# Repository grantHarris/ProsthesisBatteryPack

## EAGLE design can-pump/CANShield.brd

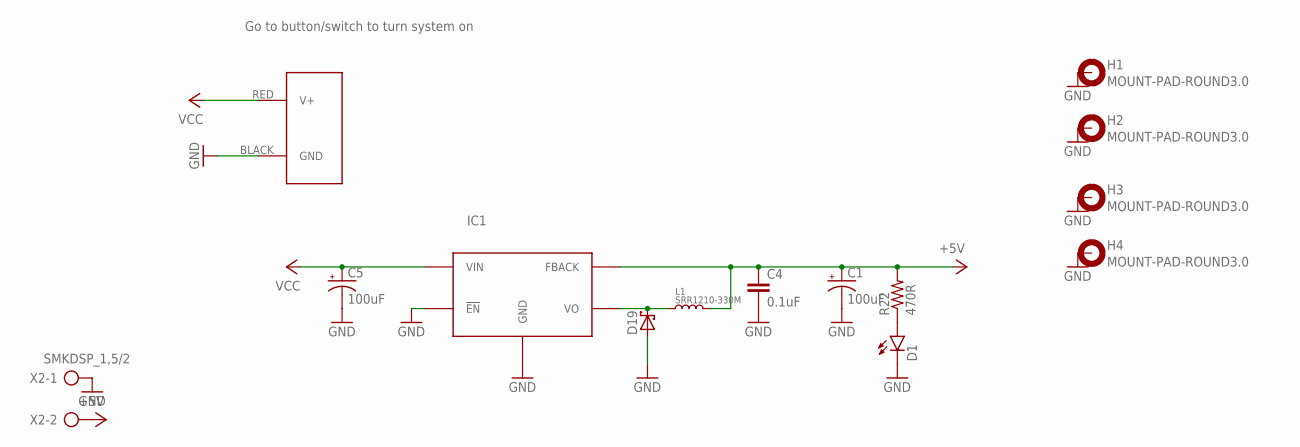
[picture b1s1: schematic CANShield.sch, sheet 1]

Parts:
C1, C5: 100uF; NIC_10X10.5_CAP
C4: 0.1uF; 0603-CAP
D1: LED1206; LED-1206
D19: SCHOTTKY-DIODESMC; SMC
H1, H2, H3, H4: MOUNT-PAD-ROUND3.0; 3,0-PAD
IC1: LM2576S; TO263-5
J1: POWERPOLE_POWER25A_HORIZONTAL_G2; POWERPOLE_PAIR_25A_HORIZ_G2
L1: SRR1210-330M; SRR1210
R22: 470R; 0603-RES
X2: SMKDSP_1,5/2

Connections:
+5V: C1.+, C4.1, IC1.4 (FBACK), L1.2, R22.2, X2.2; also elsewhere on the board
GND: C1.-, C4.2, C5.-, D1.C, D19.A, H1.B3,0, H2.B3,0, H3.B3,0, H4.B3,0, IC1.3 (GND), IC1.5 (!EN), IC1.TAB (GND), J1.BLACK (GND), X2.1; also elsewhere on the board
unnamed: D1.A, R22.1
unnamed: D19.C, IC1.2 (VO), L1.1
VCC: C5.+, IC1.1 (VIN), J1.RED (V+); also elsewhere on the board

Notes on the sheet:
Go to button/switch to turn system on

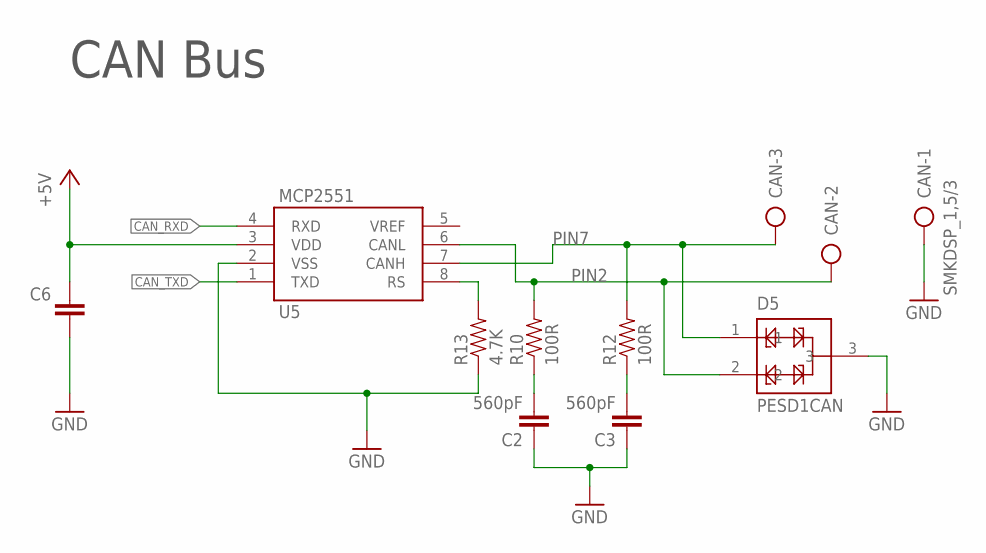
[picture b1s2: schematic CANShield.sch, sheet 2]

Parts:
C2, C3: 560pF; 0603-CAP
C6: 0.1uF; 0603-CAP
CAN: SMKDSP_1,5/3
D5: PESD1CAN; SOT23-3@1
R10, R12: 100R; 0603-RES@1
R13: 4.7K; 0603-RES@1
U5: MCP2551; SO08

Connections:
+5V: C6.2, U5.3 (VDD); also elsewhere on the board
CAN_RXD: U5.4 (RXD); also elsewhere on the board
CAN_TXD: U5.1 (TXD); also elsewhere on the board
GND: C2.1, C3.1, C6.1, CAN.1, D5.3, R13.1, U5.2 (VSS); also elsewhere on the board
unnamed: C2.2, R10.1
unnamed: C3.2, R12.1
unnamed: R13.2, U5.8 (RS)
PIN2: CAN.2, D5.2, R10.2, U5.6 (CANL)
PIN7: CAN.3, D5.1, R12.2, U5.7 (CANH)

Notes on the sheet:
CAN Bus

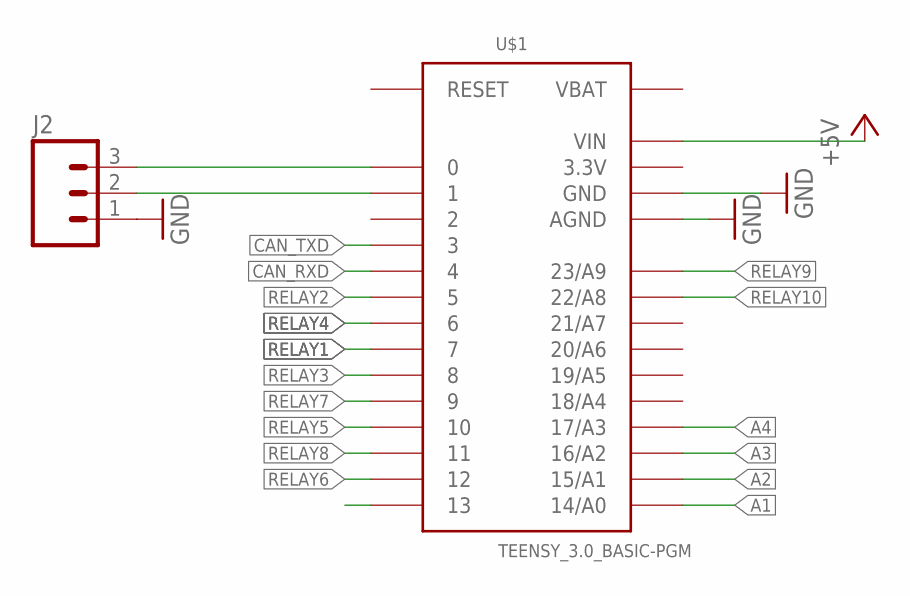
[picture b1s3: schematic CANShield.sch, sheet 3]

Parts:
J2: M03POLAR; MOLEX-1X3
U$1: TEENSY_3.0_BASIC-PGM

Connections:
3.3V: U$1.3.3V, U$1.3.3V1 (3.3V)
+5V: U$1.VIN; also elsewhere on the board
A1: U$1.14/A0; also elsewhere on the board
A2: U$1.15/A1; also elsewhere on the board
A3: U$1.16/A2; also elsewhere on the board
A4: U$1.17/A3; also elsewhere on the board
CAN_RXD: U$1.4; also elsewhere on the board
CAN_TXD: U$1.3; also elsewhere on the board
GND: J2.1, U$1.AGND, U$1.GND, U$1.GND1 (GND); also elsewhere on the board
unnamed: J2.3, U$1.0
unnamed: J2.2, U$1.1
RELAY1: U$1.7; also elsewhere on the board
RELAY2: U$1.5; also elsewhere on the board
RELAY3: U$1.8; also elsewhere on the board
RELAY4: U$1.6; also elsewhere on the board
RELAY5: U$1.10; also elsewhere on the board
RELAY6: U$1.12; also elsewhere on the board
RELAY7: U$1.9; also elsewhere on the board
RELAY8: U$1.11; also elsewhere on the board
RELAY9: U$1.23/A9; also elsewhere on the board
RELAY10: U$1.22/A8; also elsewhere on the board
VBAT: U$1.VBAT

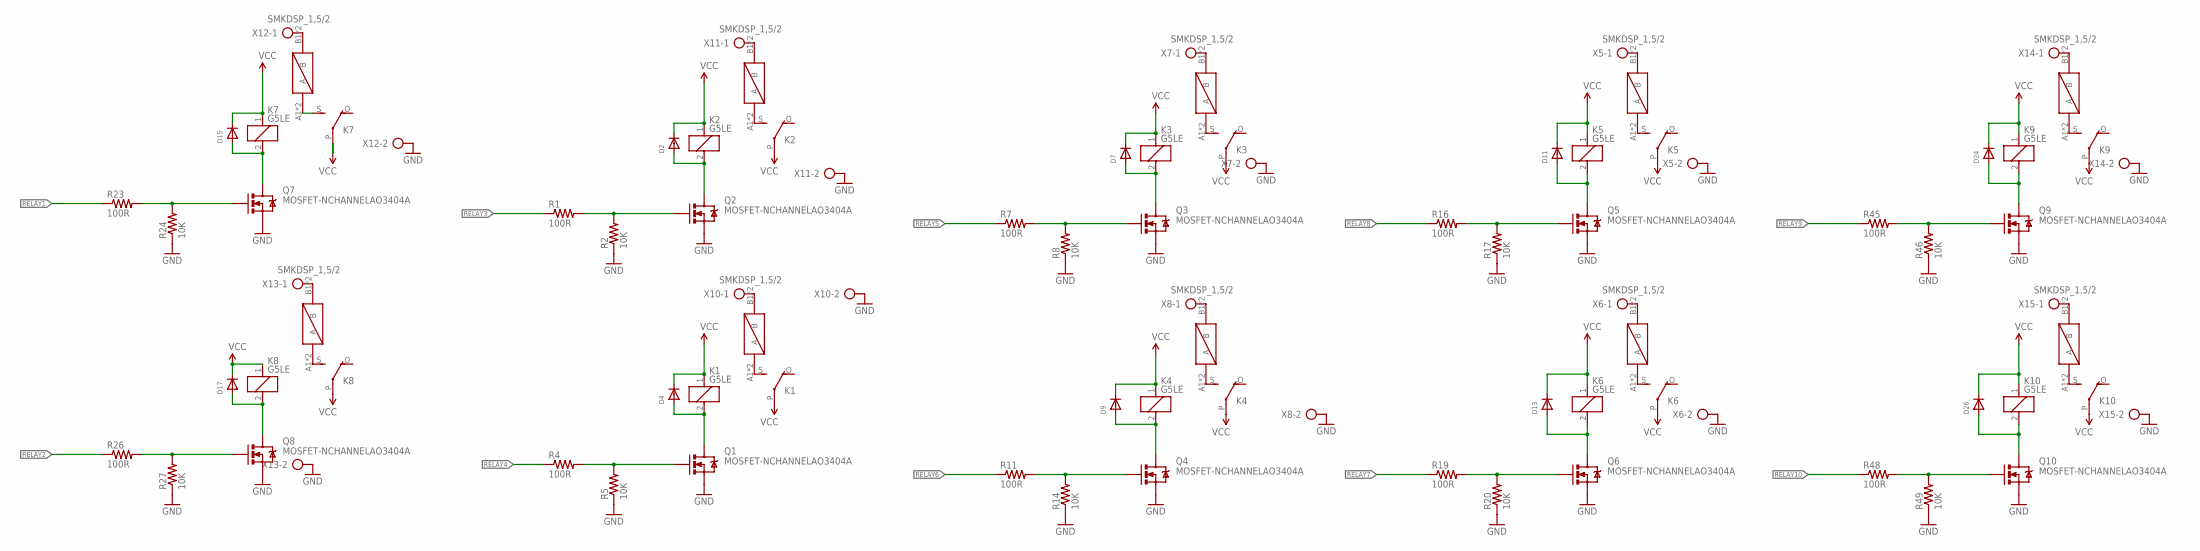
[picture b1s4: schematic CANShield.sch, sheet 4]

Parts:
D2, D4, D7, D9, D11, D13, D15, D17, D24, D26: DIODESOD-123; SOD-123
K1, K2, K3, K4, K5, K6, K7, K8, K9, K10: G5LE
Q1, Q2, Q3, Q4, Q5, Q6, Q7, Q8, Q9, Q10: MOSFET-NCHANNELAO3404A; SOT23-3
R1, R4, R7, R11, R16, R19, R23, R26, R45, R48: 100R; 0603-RES
R2, R5, R8, R14, R17, R20, R24, R27, R46, R49: 10K; 0603-RES
U$2, U$4, U$5, U$6, U$7, U$8, U$9, U$10, U$11, U$12: FUSE; MINIFUSE
X5, X6, X7, X8, X10, X11, X12, X13, X14, X15: SMKDSP_1,5/2

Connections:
GND: Q1.2 (S), Q2.2 (S), Q3.2 (S), Q4.2 (S), Q5.2 (S), Q6.2 (S), Q7.2 (S), Q8.2 (S), Q9.2 (S), Q10.2 (S), R2.1, R5.1, R8.1, R14.1, R17.1, R20.1, R24.1, R27.1, R46.1, R49.1, X5.2, X6.2, X7.2, X8.2, X10.2, X11.2, X12.2, X13.2, X14.2, X15.2; also elsewhere on the board
unnamed: Q2.1 (G), R1.2, R2.2
unnamed: D2.A, K2.2, Q2.3 (D)
unnamed: K3.S, U$7.A1 (A), U$7.A2 (A)
unnamed: K4.S, U$8.A1 (A), U$8.A2 (A)
unnamed: D4.A, K1.2, Q1.3 (D)
unnamed: Q1.1 (G), R4.2, R5.2
unnamed: U$8.B1 (B), U$8.B2 (B), X8.1
unnamed: D7.A, K3.2, Q3.3 (D)
unnamed: Q3.1 (G), R7.2, R8.2
unnamed: K6.S, U$9.A1 (A), U$9.A2 (A)
unnamed: D9.A, K4.2, Q4.3 (D)
unnamed: Q4.1 (G), R11.2, R14.2
unnamed: D11.A, K5.2, Q5.3 (D)
unnamed: Q5.1 (G), R16.2, R17.2
unnamed: D13.A, K6.2, Q6.3 (D)
unnamed: Q6.1 (G), R19.2, R20.2
unnamed: D15.A, K7.2, Q7.3 (D)
unnamed: Q7.1 (G), R23.2, R24.2
unnamed: D17.A, K8.2, Q8.3 (D)
unnamed: Q8.1 (G), R26.2, R27.2
unnamed: K2.S, U$4.A1 (A), U$4.A2 (A)
unnamed: K8.S, U$5.A1 (A), U$5.A2 (A)
unnamed: K7.S, U$2.A1 (A), U$2.A2 (A)
unnamed: K1.S, U$6.A1 (A), U$6.A2 (A)
unnamed: D24.A, K9.2, Q9.3 (D)
unnamed: Q9.1 (G), R45.2, R46.2
unnamed: D26.A, K10.2, Q10.3 (D)
unnamed: Q10.1 (G), R48.2, R49.2
unnamed: K9.S, U$11.A1 (A), U$11.A2 (A)
unnamed: K10.S, U$12.A1 (A), U$12.A2 (A)
unnamed: U$2.B1 (B), U$2.B2 (B), X12.1
unnamed: U$5.B1 (B), U$5.B2 (B), X13.1
unnamed: U$4.B1 (B), U$4.B2 (B), X11.1
unnamed: U$6.B1 (B), U$6.B2 (B), X10.1
unnamed: U$9.B1 (B), U$9.B2 (B), X6.1
unnamed: K5.S, U$10.A1 (A), U$10.A2 (A)
unnamed: U$7.B1 (B), U$7.B2 (B), X7.1
unnamed: U$10.B1 (B), U$10.B2 (B), X5.1
unnamed: U$12.B1 (B), U$12.B2 (B), X15.1
unnamed: U$11.B1 (B), U$11.B2 (B), X14.1
RELAY1: R23.1; also elsewhere on the board
RELAY2: R26.1; also elsewhere on the board
RELAY3: R1.1; also elsewhere on the board
RELAY4: R4.1; also elsewhere on the board
RELAY5: R7.1; also elsewhere on the board
RELAY6: R11.1; also elsewhere on the board
RELAY7: R19.1; also elsewhere on the board
RELAY8: R16.1; also elsewhere on the board
RELAY9: R45.1; also elsewhere on the board
RELAY10: R48.1; also elsewhere on the board
VCC: D2.C, D4.C, D7.C, D9.C, D11.C, D13.C, D15.C, D17.C, D24.C, D26.C, K1.1, K1.P, K2.1, K2.P, K3.1, K3.P, K4.1, K4.P, K5.1, K5.P, K6.1, K6.P, K7.1, K7.P, K8.1, K8.P, K9.1, K9.P, K10.1, K10.P; also elsewhere on the board

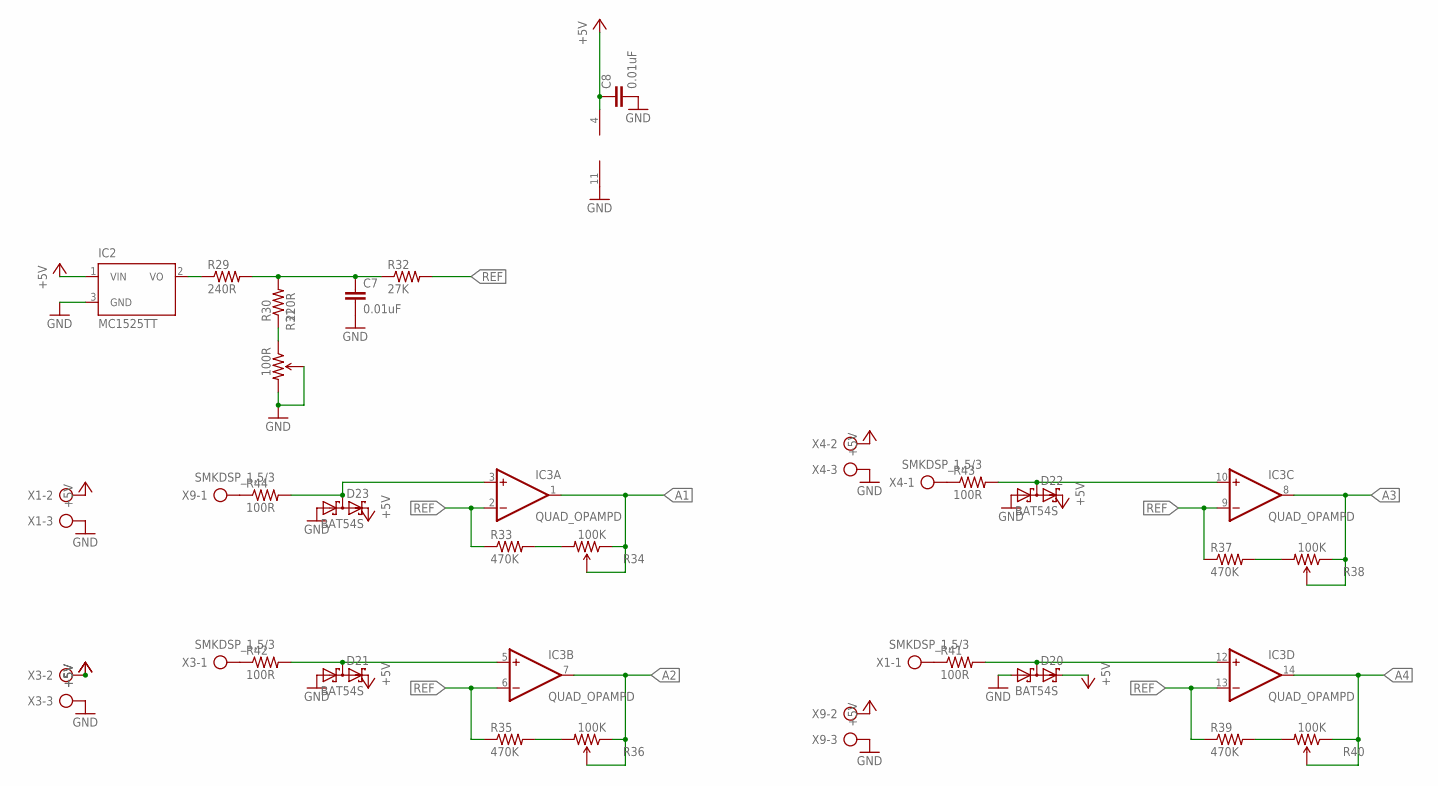
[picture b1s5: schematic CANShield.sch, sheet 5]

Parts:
C7, C8: 0.01uF; 0603-CAP
D20, D21, D22, D23: BAT54S; SOT23
IC2: MC1525TT; SOT23
IC3: QUAD_OPAMPD; SO14
R29: 240R; 0603-RES
R30: 220R; 0603-RES
R31: 100R; TRIMPOT-3MM
R32: 27K; 0603-RES
R33, R35, R37, R39: 470K; 0603-RES
R34, R36, R38, R40: 100K; TRIMPOT-3MM
R41, R42, R43, R44: 100R; 0603-RES
X1, X3, X4, X9: SMKDSP_1,5/3

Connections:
+5V: C8.1, D20.2 (C2), D21.2 (C2), D22.2 (C2), D23.2 (C2), IC2.1 (VIN), IC3.4 (V+), X1.2, X3.2, X4.2, X9.2; also elsewhere on the board
A1: IC3.1 (OUT), R34.1 (CCW), R34.2 (WIPER); also elsewhere on the board
A2: IC3.7 (OUT), R36.1 (CCW), R36.2 (WIPER); also elsewhere on the board
A3: IC3.8 (OUT), R38.1 (CCW), R38.2 (WIPER); also elsewhere on the board
A4: IC3.14 (OUT), R40.1 (CCW), R40.2 (WIPER); also elsewhere on the board
GND: C7.2, C8.2, D20.1 (A1), D21.1 (A1), D22.1 (A1), D23.1 (A1), IC2.3 (GND), IC3.11 (V-), R31.2 (WIPER), R31.3 (CW), X1.3, X3.3, X4.3, X9.3; also elsewhere on the board
unnamed: R44.1, X9.1
unnamed: R42.1, X3.1
unnamed: R43.1, X4.1
unnamed: R41.1, X1.1
unnamed: IC2.2 (VO), R29.1
unnamed: C7.1, R29.2, R30.2, R32.1
unnamed: R30.1, R31.1 (CCW)
unnamed: R33.2, R34.3 (CW)
unnamed: D21.3 (C1A2), IC3.5 (+IN), R42.2
unnamed: D20.3 (C1A2), IC3.12 (+IN), R41.2
unnamed: R35.2, R36.3 (CW)
unnamed: D23.3 (C1A2), IC3.3 (+IN), R44.2
unnamed: R39.2, R40.3 (CW)
unnamed: R37.2, R38.3 (CW)
unnamed: D22.3 (C1A2), IC3.10 (+IN), R43.2
REF: IC3.2 (-IN), IC3.6 (-IN), IC3.9 (-IN), IC3.13 (-IN), R32.2, R33.1, R35.1, R37.1, R39.1

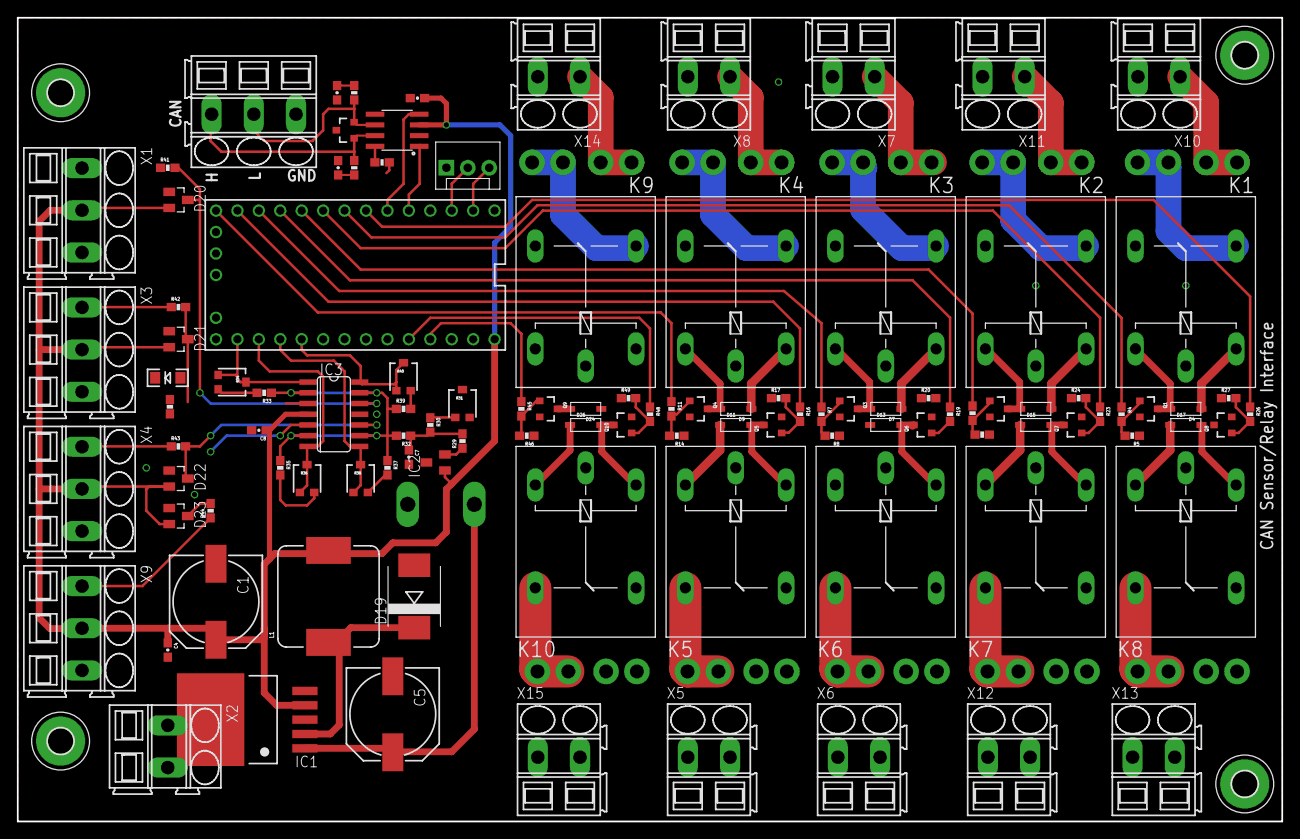
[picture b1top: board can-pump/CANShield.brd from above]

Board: 2 copper layers, 149.9 x 95.2 mm, 124 parts (1 on the bottom side), 85 nets.

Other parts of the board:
U$3: PROS_LOGO

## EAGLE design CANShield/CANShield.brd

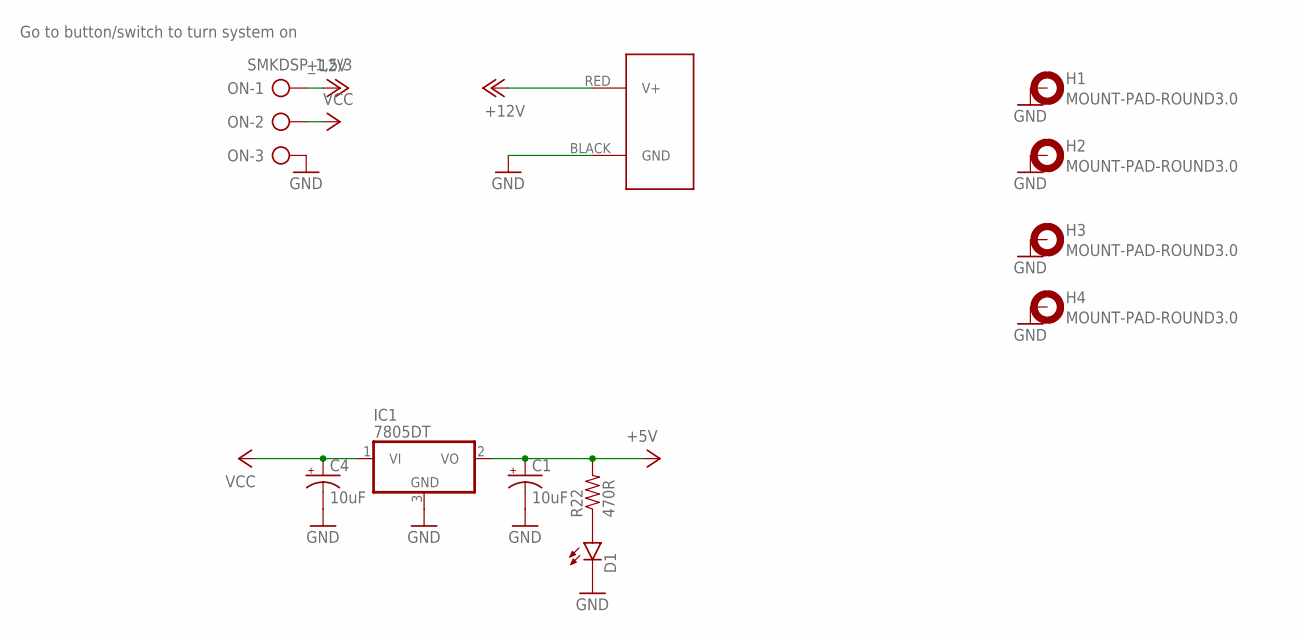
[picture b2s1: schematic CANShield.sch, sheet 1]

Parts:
C1, C4: 10uF; PANASONIC_C
D1: LED1206; LED-1206
H1, H2, H3, H4: MOUNT-PAD-ROUND3.0; 3,0-PAD
IC1: 7805DT; TO252
J2: POWERPOLE_POWER25A_HORIZONTAL_G2; POWERPOLE_PAIR_25A_HORIZ_G2
ON: SMKDSP_1,5/3
R22: 470R; 0603-RES

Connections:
+5V: C1.+, IC1.2 (VO), R22.2; also elsewhere on the board
+12V: J2.RED (V+), ON.1; also elsewhere on the board
GND: C1.-, C4.-, D1.C, H1.B3,0, H2.B3,0, H3.B3,0, H4.B3,0, IC1.3 (GND), J2.BLACK (GND), ON.3; also elsewhere on the board
unnamed: D1.A, R22.1
VCC: C4.+, IC1.1 (VI), ON.2

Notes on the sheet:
Go to button/switch to turn system on

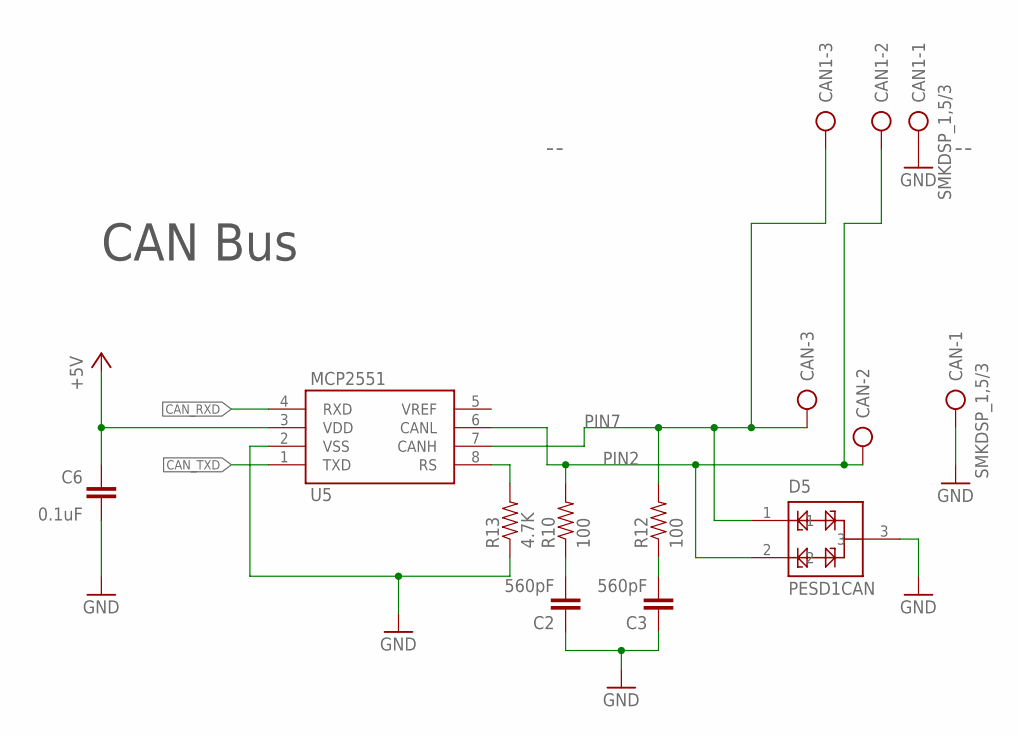
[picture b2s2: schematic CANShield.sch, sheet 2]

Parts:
C2, C3: 560pF; 0603-CAP
C6: 0.1uF; 0603-CAP
CAN, CAN1: SMKDSP_1,5/3
D5: PESD1CAN; SOT23-3@1
R10, R12: 100; 0603-RES@1
R13: 4.7K; 0603-RES@1
U5: MCP2551; SO08

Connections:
+5V: C6.2, U5.3 (VDD); also elsewhere on the board
CAN_RXD: U5.4 (RXD); also elsewhere on the board
CAN_TXD: U5.1 (TXD); also elsewhere on the board
GND: C2.1, C3.1, C6.1, CAN.1, CAN1.1, D5.3, R13.1, U5.2 (VSS); also elsewhere on the board
unnamed: C2.2, R10.1
unnamed: C3.2, R12.1
unnamed: R13.2, U5.8 (RS)
PIN2: CAN.2, CAN1.2, D5.2, R10.2, U5.6 (CANL)
PIN7: CAN.3, CAN1.3, D5.1, R12.2, U5.7 (CANH)

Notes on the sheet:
CAN Bus

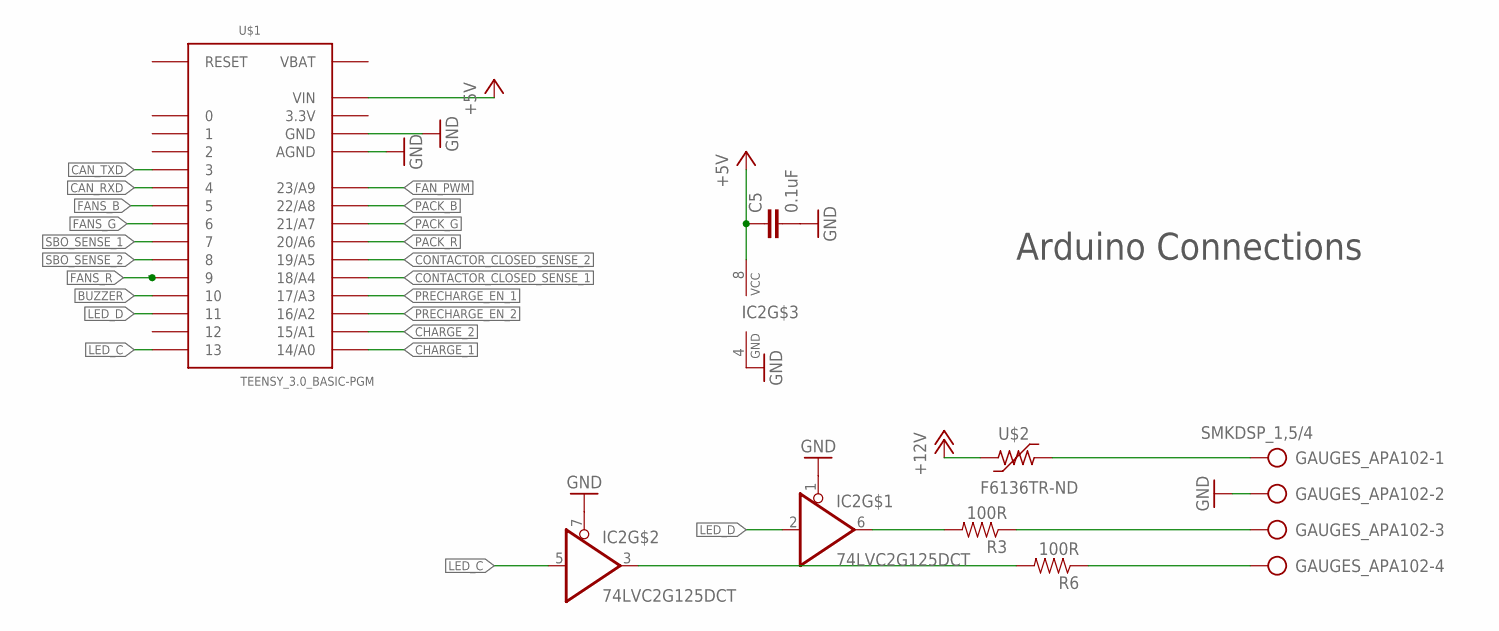
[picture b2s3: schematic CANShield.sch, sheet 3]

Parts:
C5: 0.1uF; 0603-CAP
GAUGES_APA102: SMKDSP_1,5/4
IC2: 74LVC2G125DCT; SSOP08
R3, R6: 100R; 0603-RES
U$1: TEENSY_3.0_BASIC-PGM
U$2: F6136TR-ND; 2920L

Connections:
3.3V: U$1.3.3V, U$1.3.3V1 (3.3V)
+5V: C5.1, IC2.8 (VCC), U$1.VIN; also elsewhere on the board
+12V: U$2.1; also elsewhere on the board
BUZZER: U$1.10; also elsewhere on the board
CAN_RXD: U$1.4; also elsewhere on the board
CAN_TXD: U$1.3; also elsewhere on the board
CHARGE_1: U$1.14/A0; also elsewhere on the board
CHARGE_2: U$1.15/A1; also elsewhere on the board
CONTACTOR_CLOSED_SENSE_1: U$1.18/A4; also elsewhere on the board
CONTACTOR_CLOSED_SENSE_2: U$1.19/A5; also elsewhere on the board
FANS_B: U$1.5; also elsewhere on the board
FANS_G: U$1.6; also elsewhere on the board
FANS_R: U$1.9; also elsewhere on the board
FAN_PWM: U$1.23/A9; also elsewhere on the board
GND: C5.2, GAUGES_APA102.2, IC2.1 (OE), IC2.4 (GND), IC2.7 (OE), U$1.AGND, U$1.GND, U$1.GND1 (GND); also elsewhere on the board
LED_C: IC2.5 (I), U$1.13
LED_D: IC2.2 (I), U$1.11
unnamed: IC2.3 (O), R6.2
unnamed: GAUGES_APA102.3, R3.1
unnamed: GAUGES_APA102.4, R6.1
unnamed: IC2.6 (O), R3.2
unnamed: GAUGES_APA102.1, U$2.2
PACK_B: U$1.22/A8; also elsewhere on the board
PACK_G: U$1.21/A7; also elsewhere on the board
PACK_R: U$1.20/A6; also elsewhere on the board
PRECHARGE_EN_1: U$1.17/A3; also elsewhere on the board
PRECHARGE_EN_2: U$1.16/A2; also elsewhere on the board
SBO_SENSE_1: U$1.7; also elsewhere on the board
SBO_SENSE_2: U$1.8; also elsewhere on the board
VBAT: U$1.VBAT

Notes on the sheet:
Arduino Connections

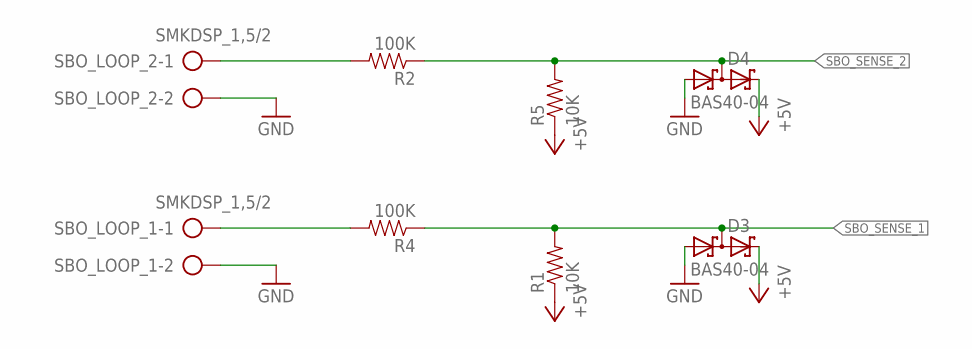
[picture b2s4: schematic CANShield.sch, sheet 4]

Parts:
D3, D4: BAS40-04; SOT23
R1, R5: 10K; 0603-RES
R2, R4: 100K; 0603-RES
SBO_LOOP_1, SBO_LOOP_2: SMKDSP_1,5/2

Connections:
+5V: D3.2 (C2), D4.2 (C2), R1.1, R5.1; also elsewhere on the board
GND: D3.1 (A1), D4.1 (A1), SBO_LOOP_1.2, SBO_LOOP_2.2; also elsewhere on the board
unnamed: R2.2, SBO_LOOP_2.1
unnamed: R4.2, SBO_LOOP_1.1
SBO_SENSE_1: D3.3 (C1A2), R1.2, R4.1; also elsewhere on the board
SBO_SENSE_2: D4.3 (C1A2), R2.1, R5.2; also elsewhere on the board

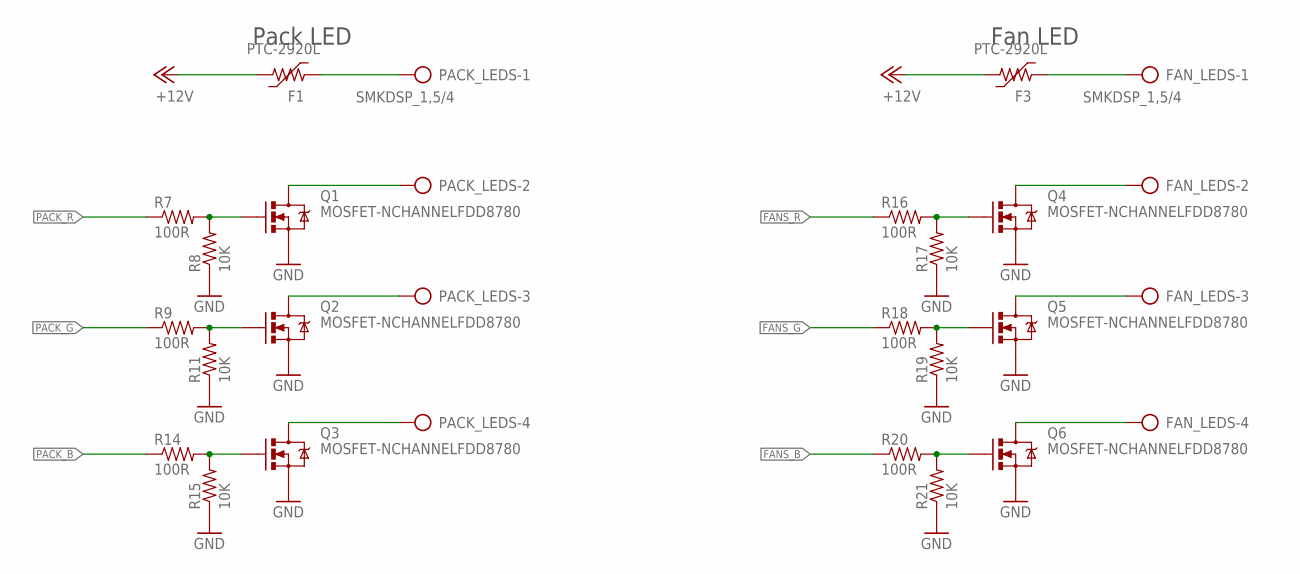
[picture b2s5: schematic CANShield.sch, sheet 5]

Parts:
F1, F3: PTC-2920L; 2920L
FAN_LEDS: SMKDSP_1,5/4
PACK_LEDS: SMKDSP_1,5/4
Q1, Q2, Q3, Q4, Q5, Q6: MOSFET-NCHANNELFDD8780; DPAK
R7, R9, R14, R16, R18, R20: 100R; 0603-RES
R8, R11, R15, R17, R19, R21: 10K; 0603-RES

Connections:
+12V: F1.2, F3.2; also elsewhere on the board
FANS_B: R20.1; also elsewhere on the board
FANS_G: R18.1; also elsewhere on the board
FANS_R: R16.1; also elsewhere on the board
GND: Q1.3 (S), Q2.3 (S), Q3.3 (S), Q4.3 (S), Q5.3 (S), Q6.3 (S), R8.1, R11.1, R15.1, R17.1, R19.1, R21.1; also elsewhere on the board
unnamed: PACK_LEDS.2, Q1.4 (D)
unnamed: F1.1, PACK_LEDS.1
unnamed: PACK_LEDS.3, Q2.4 (D)
unnamed: PACK_LEDS.4, Q3.4 (D)
unnamed: Q1.1 (G), R7.2, R8.2
unnamed: Q2.1 (G), R9.2, R11.2
unnamed: Q3.1 (G), R14.2, R15.2
unnamed: F3.1, FAN_LEDS.1
unnamed: FAN_LEDS.2, Q4.4 (D)
unnamed: FAN_LEDS.3, Q5.4 (D)
unnamed: FAN_LEDS.4, Q6.4 (D)
unnamed: Q4.1 (G), R16.2, R17.2
unnamed: Q5.1 (G), R18.2, R19.2
unnamed: Q6.1 (G), R20.2, R21.2
PACK_B: R14.1; also elsewhere on the board
PACK_G: R9.1; also elsewhere on the board
PACK_R: R7.1; also elsewhere on the board

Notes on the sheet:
Pack LED
Fan LED

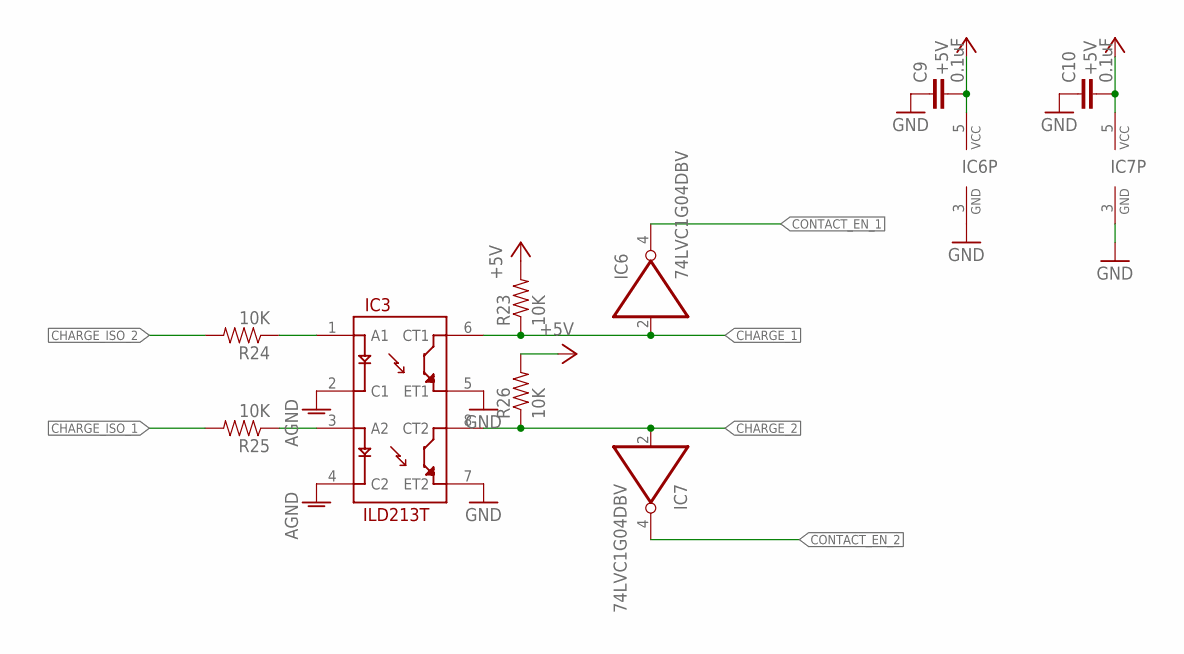
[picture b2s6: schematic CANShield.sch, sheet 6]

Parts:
C9, C10: 0.1uF; 0603-CAP
IC3: ILD213T; SO08
IC6, IC7: 74LVC1G04DBV; SOT23-5
R23, R24, R25, R26: 10K; 0603-RES

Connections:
+5V: C9.2, C10.2, IC6.5 (VCC), IC7.5 (VCC), R23.2, R26.2; also elsewhere on the board
AGND: IC3.2 (C1), IC3.4 (C2); also elsewhere on the board
CHARGE_1: IC3.6 (CT1), IC6.2 (I), R23.1; also elsewhere on the board
CHARGE_2: IC3.8 (CT2), IC7.2 (I), R26.1; also elsewhere on the board
CHARGE_ISO_1: R25.2; also elsewhere on the board
CHARGE_ISO_2: R24.2; also elsewhere on the board
CONTACT_EN_1: IC6.4 (O); also elsewhere on the board
CONTACT_EN_2: IC7.4 (O); also elsewhere on the board
GND: C9.1, C10.1, IC3.5 (ET1), IC3.7 (ET2), IC6.3 (GND), IC7.3 (GND); also elsewhere on the board
unnamed: IC3.3 (A2), R25.1
unnamed: IC3.1 (A1), R24.1

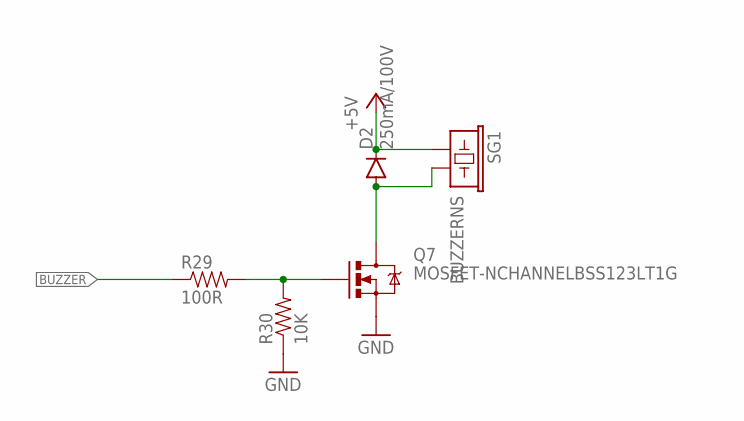
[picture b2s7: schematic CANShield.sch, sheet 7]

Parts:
D2: 250mA/100V; SOD-323
Q7: MOSFET-NCHANNELBSS123LT1G; SOT23
R29: 100R; 0603-RES
R30: 10K; 0603-RES
SG1: BUZZERNS; BUZZER-12MM-NS

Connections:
+5V: D2.C, SG1.+ (1); also elsewhere on the board
BUZZER: R29.1; also elsewhere on the board
GND: Q7.2 (S), R30.1; also elsewhere on the board
unnamed: D2.A, Q7.3 (D), SG1.- (2)
unnamed: Q7.1 (G), R29.2, R30.2

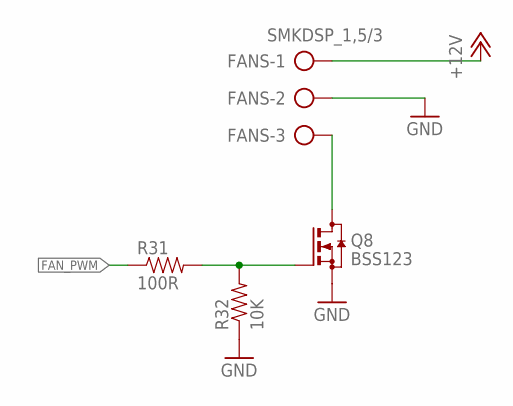
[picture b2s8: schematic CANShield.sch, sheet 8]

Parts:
FANS: SMKDSP_1,5/3
Q8: BSS123; SOT23
R31: 100R; 0603-RES
R32: 10K; 0603-RES

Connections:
+12V: FANS.1; also elsewhere on the board
FAN_PWM: R31.1; also elsewhere on the board
GND: FANS.2, Q8.2 (S), R32.1; also elsewhere on the board
unnamed: Q8.1 (G), R31.2, R32.2
unnamed: FANS.3, Q8.3 (D)

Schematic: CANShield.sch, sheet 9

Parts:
74HC125M: MM74HC125M; SOIC127P600X175-14N
D6, D7: DIODESOD123; SOD-123
D12, D13: BAS40-04; SOT23
F2: PTCTHERMISTOR1206; PTC-1206
LM393M: LM393M; SOIC127P600X180-8N
PRECHARGE_FUSE: FUSEX20MM; FUSE_5MM
PRECHARGE_RELAY, PRECHARGE_RELAY1: DS2Y-S-DC5V; DS2Y
Q9, Q11: IRLML6344TRPBF; SOT23
R33, R45: 100k; 0603-RES
R34, R41: 10k; 0603-RES
R36, R37, R42: 470k; 0805
R38, R43: 13K; 0805
R39: 110k; 0805
R40: 12K; 0805
R48, R49: 100R; 0603-RES
U$5: REE-0505S
X2, X3, X4, X5: SMKDSP_1,5/2
X6: SMKDSP_1,5/4

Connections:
5V: 74HC125M.14 (VCC), LM393M.8 (VCC), R33.1, R45.1, U$5.+VOUT
96V_IN_FUSED: PRECHARGE_FUSE.1, PRECHARGE_RELAY.8 (S), PRECHARGE_RELAY1.8 (S), R37.2
+5V: D6.C, D7.C, D12.2 (C2), D13.2 (C2), F2.2, PRECHARGE_RELAY.1 (+), PRECHARGE_RELAY1.1 (+), U$5.+VIN; also elsewhere on the board
AGND: 74HC125M.1 (C1), 74HC125M.4 (C2), 74HC125M.7 (GND), 74HC125M.10 (C3), 74HC125M.13 (C4), LM393M.4 (GND), PRECHARGE_RELAY.11 (O), PRECHARGE_RELAY1.11 (O), R38.1, R40.1, R43.1, U$5.-VOUT, X4.2; also elsewhere on the board
CAP_CHARGE_REF: LM393M.2 (IN1_(-)), LM393M.6 (IN2_(-)), R39.1, R40.2
CAP_CHARGE_V_CURR_1: LM393M.3 (IN1_(+)), R36.1, R38.2
CAP_CHARGE_V_CURR_2: LM393M.5 (IN2_(+)), R42.1, R43.2
CHARGE_ISO_1: 74HC125M.3 (Y1); also elsewhere on the board
CHARGE_ISO_2: 74HC125M.8 (Y3); also elsewhere on the board
GND: D12.1 (A1), D13.1 (A1), Q9.2 (S), Q11.2 (S), R34.2, R41.2, U$5.-VIN, X6.1; also elsewhere on the board
unnamed: R37.1, R39.2
unnamed: 74HC125M.9 (A3), 74HC125M.12 (A4), LM393M.7 (OUT2), R45.2
unnamed: R48.1, X6.4
unnamed: R49.1, X6.3
unnamed: PRECHARGE_RELAY.13, X2.1
unnamed: PRECHARGE_RELAY1.13, X3.1
unnamed: PRECHARGE_FUSE.3 (2), X4.1
unnamed: F2.1, X6.2
PRECHARGE_EN_1: D13.3 (C1A2), Q9.1 (G), R34.1, R48.2; also elsewhere on the board
PRECHARGE_EN_2: D12.3 (C1A2), Q11.1 (G), R41.1, R49.2; also elsewhere on the board
PRECHARGE_OUT_1: PRECHARGE_RELAY.6 (O), PRECHARGE_RELAY.9 (S), R36.2, X5.1
PRECHARGE_OUT_2: PRECHARGE_RELAY1.6 (O), PRECHARGE_RELAY1.9 (S), R42.2, X5.2
PRECHARGE_RESISTOR_IN_1: PRECHARGE_RELAY.4, X2.2
PRECHARGE_RESISTOR_IN_2: PRECHARGE_RELAY1.4, X3.2
PRECH_DRAIN: D6.A, PRECHARGE_RELAY.16 (-), Q9.3 (D)
PRECH_DRAIN1: D7.A, PRECHARGE_RELAY1.16 (-), Q11.3 (D)
PRECH_STATE_TO_BUFF: 74HC125M.2 (A1), 74HC125M.5 (A2), LM393M.1 (OUT1), R33.2

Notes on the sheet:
*Output goes HIGH (5V) when cap charge goes ABOVE reference
Part #1A3399-10 from Mouser. Must order in multiples of 2

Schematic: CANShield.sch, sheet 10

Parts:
CONTACTOR_1, CONTACTOR_2: SMKDSP_1,5/4
D8, D9: BAS40-04; SOT23
D10, D11: DIODESOD123; SOD-123
PF1, PF2: PTC-2920L; 2920L
Q13, Q14: IRLML6344TRPBF; SOT23
R27, R28: 10K; 0603-RES
R35, R44: 100K; 0603-RES
R46, R47: 10k; 0603-RES
U$7, U$8: RELAY-2G5Q; RELAY-G5V
X1: SMKDSP_1,5/2

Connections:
+5V: D8.2 (C2), D9.2 (C2), R27.1, R28.1; also elsewhere on the board
+12V: D10.C, D11.C, PF1.1, PF2.1, U$7.2, U$8.2; also elsewhere on the board
CONTACTOR_CLOSED_SENSE_1: D8.3 (C1A2), R27.2, R44.1; also elsewhere on the board
CONTACTOR_CLOSED_SENSE_2: D9.3 (C1A2), R28.2, R35.1; also elsewhere on the board
CONTACTOR_GND: U$7.10, U$8.10, X1.1
CONTACT_EN_1: Q13.1 (G), R46.1; also elsewhere on the board
CONTACT_EN_2: Q14.1 (G), R47.1; also elsewhere on the board
GND: CONTACTOR_1.1, CONTACTOR_2.1, D8.1 (A1), D9.1 (A1), Q13.2 (S), Q14.2 (S), R46.2, R47.2, X1.2; also elsewhere on the board
unnamed: D10.A, Q14.3 (D), U$8.9
unnamed: D11.A, Q13.3 (D), U$7.9
unnamed: CONTACTOR_1.3, U$7.5, U$7.6
unnamed: CONTACTOR_2.3, U$8.5, U$8.6
unnamed: CONTACTOR_1.4, PF2.2
unnamed: CONTACTOR_2.4, PF1.2
unnamed: CONTACTOR_2.2, R35.2
unnamed: CONTACTOR_1.2, R44.2

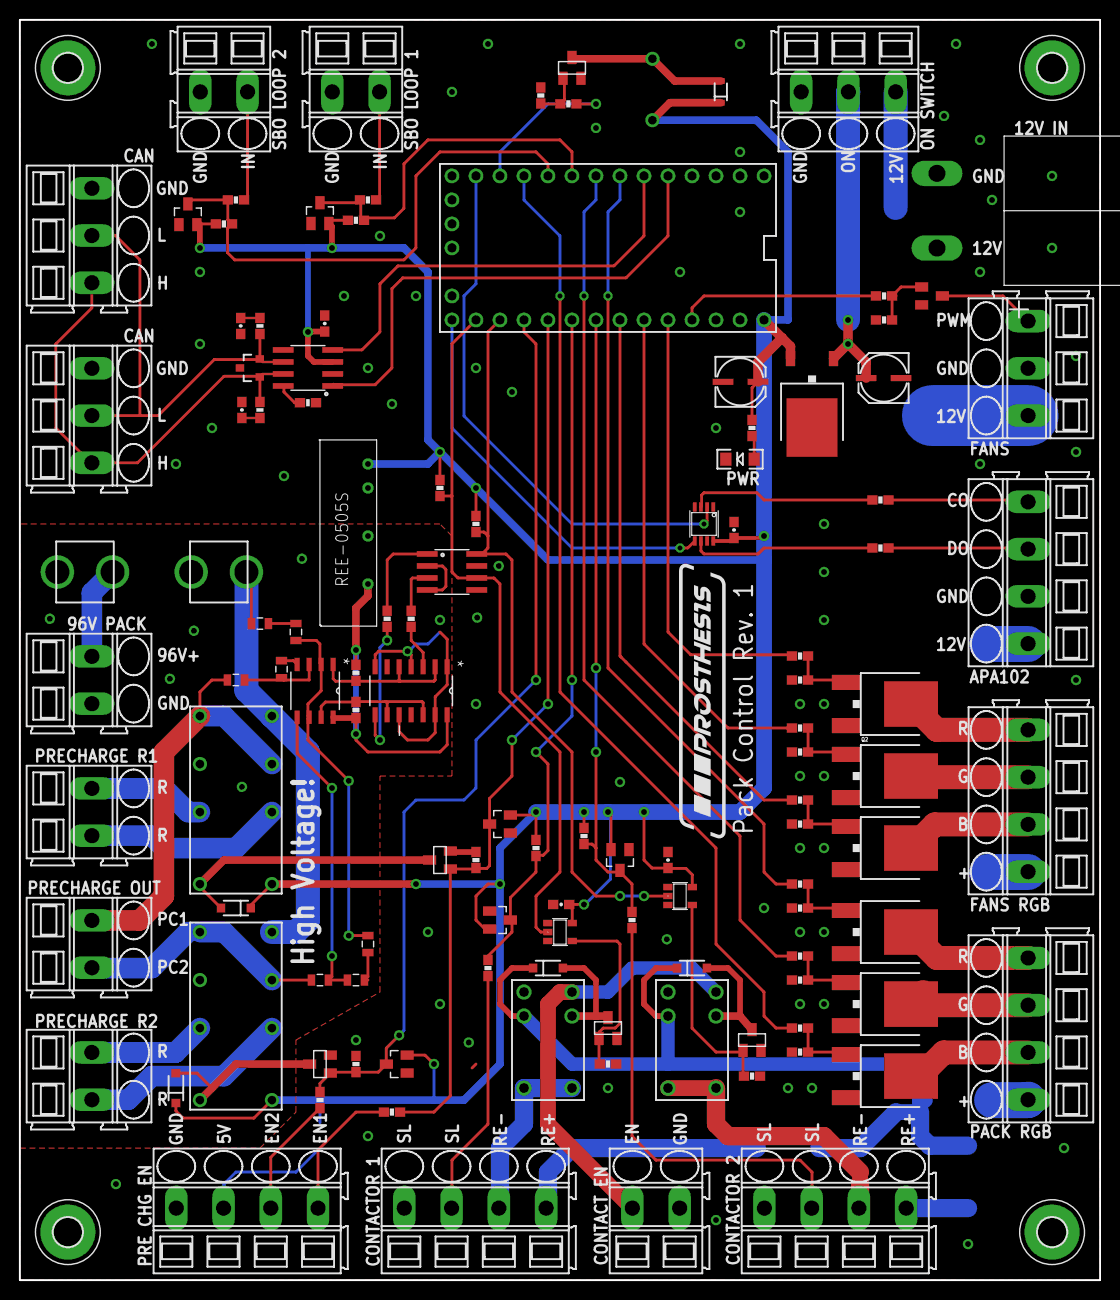
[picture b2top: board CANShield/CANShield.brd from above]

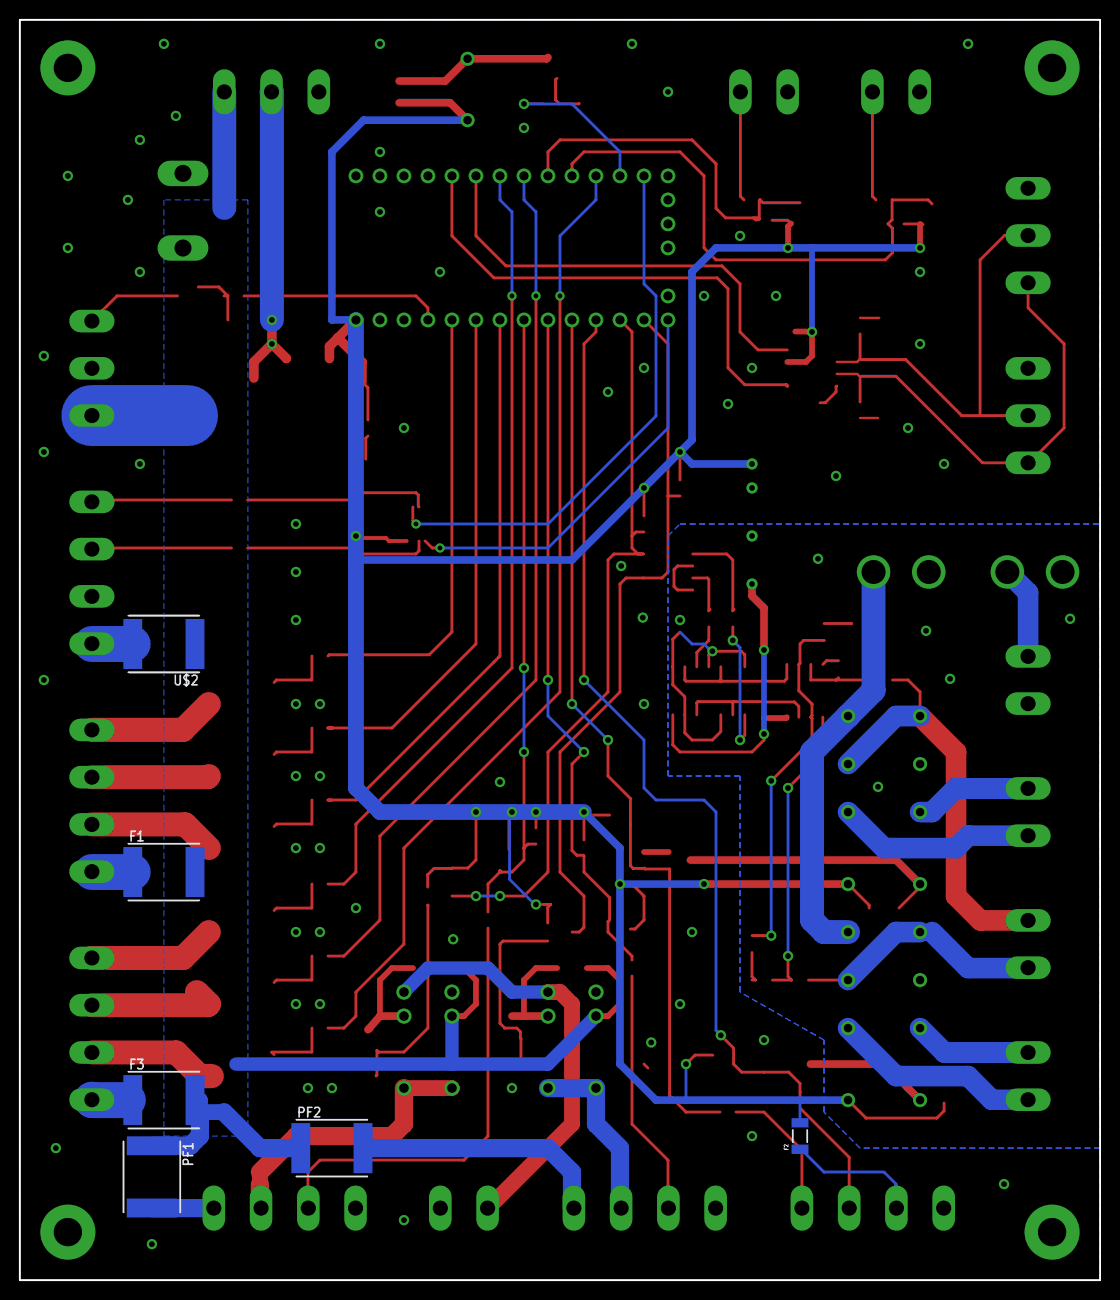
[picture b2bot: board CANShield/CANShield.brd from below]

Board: 2 copper layers, 114.3 x 133.3 mm, 127 parts (6 on the bottom side), 92 nets.

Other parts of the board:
U$4: PROS_LOGO

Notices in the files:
parts and their libraries:
SparkFun-DigitalIC: Licensing: Creative Commons ShareAlike 4.0 International - https://creativecommons.org/licenses/by-sa/4.0
polyswitch: Copyright (C) 2008, Bob Starr
SparkFun-Aesthetics: Licensing: CC v3.0 Share-Alike You are welcome to use this library for commercial purposes.
